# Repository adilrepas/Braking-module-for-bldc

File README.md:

Simple Braking Resistor For BLDC Controller

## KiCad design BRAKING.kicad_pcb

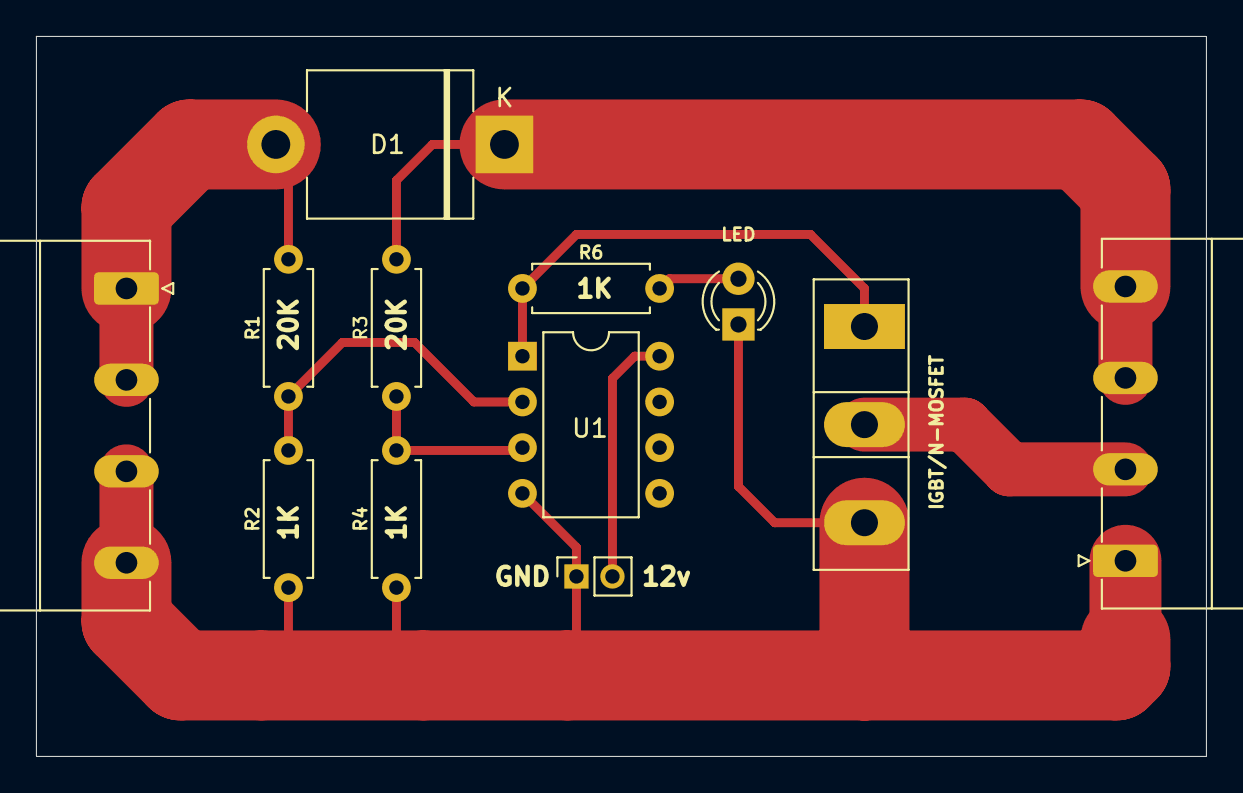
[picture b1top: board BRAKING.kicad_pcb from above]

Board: 2 copper layers, 65.0 x 40.0 mm, 12 parts (0 on the bottom side), 9 nets.

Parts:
D1: D_Small; D_5KPW_P12.70mm_Horizontal
J1, J2: Screw_Terminal_01x04; PhoenixContact_MC_1,5_4-G-5.08_1x04_P5.08mm_Horizontal
J3: Conn_01x02; PinSocket_1x02_P2.00mm_Vertical
LED: LED; LED_D3.0mm
Q1: IRLZ44N; TO-247-3_Vertical
R1, R3: 20K; R_Axial_DIN0207_L6.3mm_D2.5mm_P7.62mm_Horizontal
R2, R4, R6: 1K; R_Axial_DIN0207_L6.3mm_D2.5mm_P7.62mm_Horizontal
U1: LM358; DIP-8_W7.62mm

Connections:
+12V: J3.2, U1.8
GND: J1.3, J1.4, J2.1, J3.1, LED.1, Q1.3, R2.2, R4.2, U1.4
unnamed: D1.1, J2.3, J2.4, R3.2
unnamed: D1.2, J1.1, J1.2, R1.2
unnamed: LED.2, R6.2
unnamed: Q1.1, R6.1, U1.1
unnamed: R1.1, R2.1, U1.2
unnamed: R3.1, R4.1, U1.3
R-: J2.2, Q1.2

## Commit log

2022-03-01 Create Test
2022-03-01 Rename FFBOARD.kicad_pcb to Braking.kicad_pcb
2022-03-01 Rename FFBOARD.pro to Braking.pro
2022-03-01 Rename FFBOARD.sch to Braking.sch
